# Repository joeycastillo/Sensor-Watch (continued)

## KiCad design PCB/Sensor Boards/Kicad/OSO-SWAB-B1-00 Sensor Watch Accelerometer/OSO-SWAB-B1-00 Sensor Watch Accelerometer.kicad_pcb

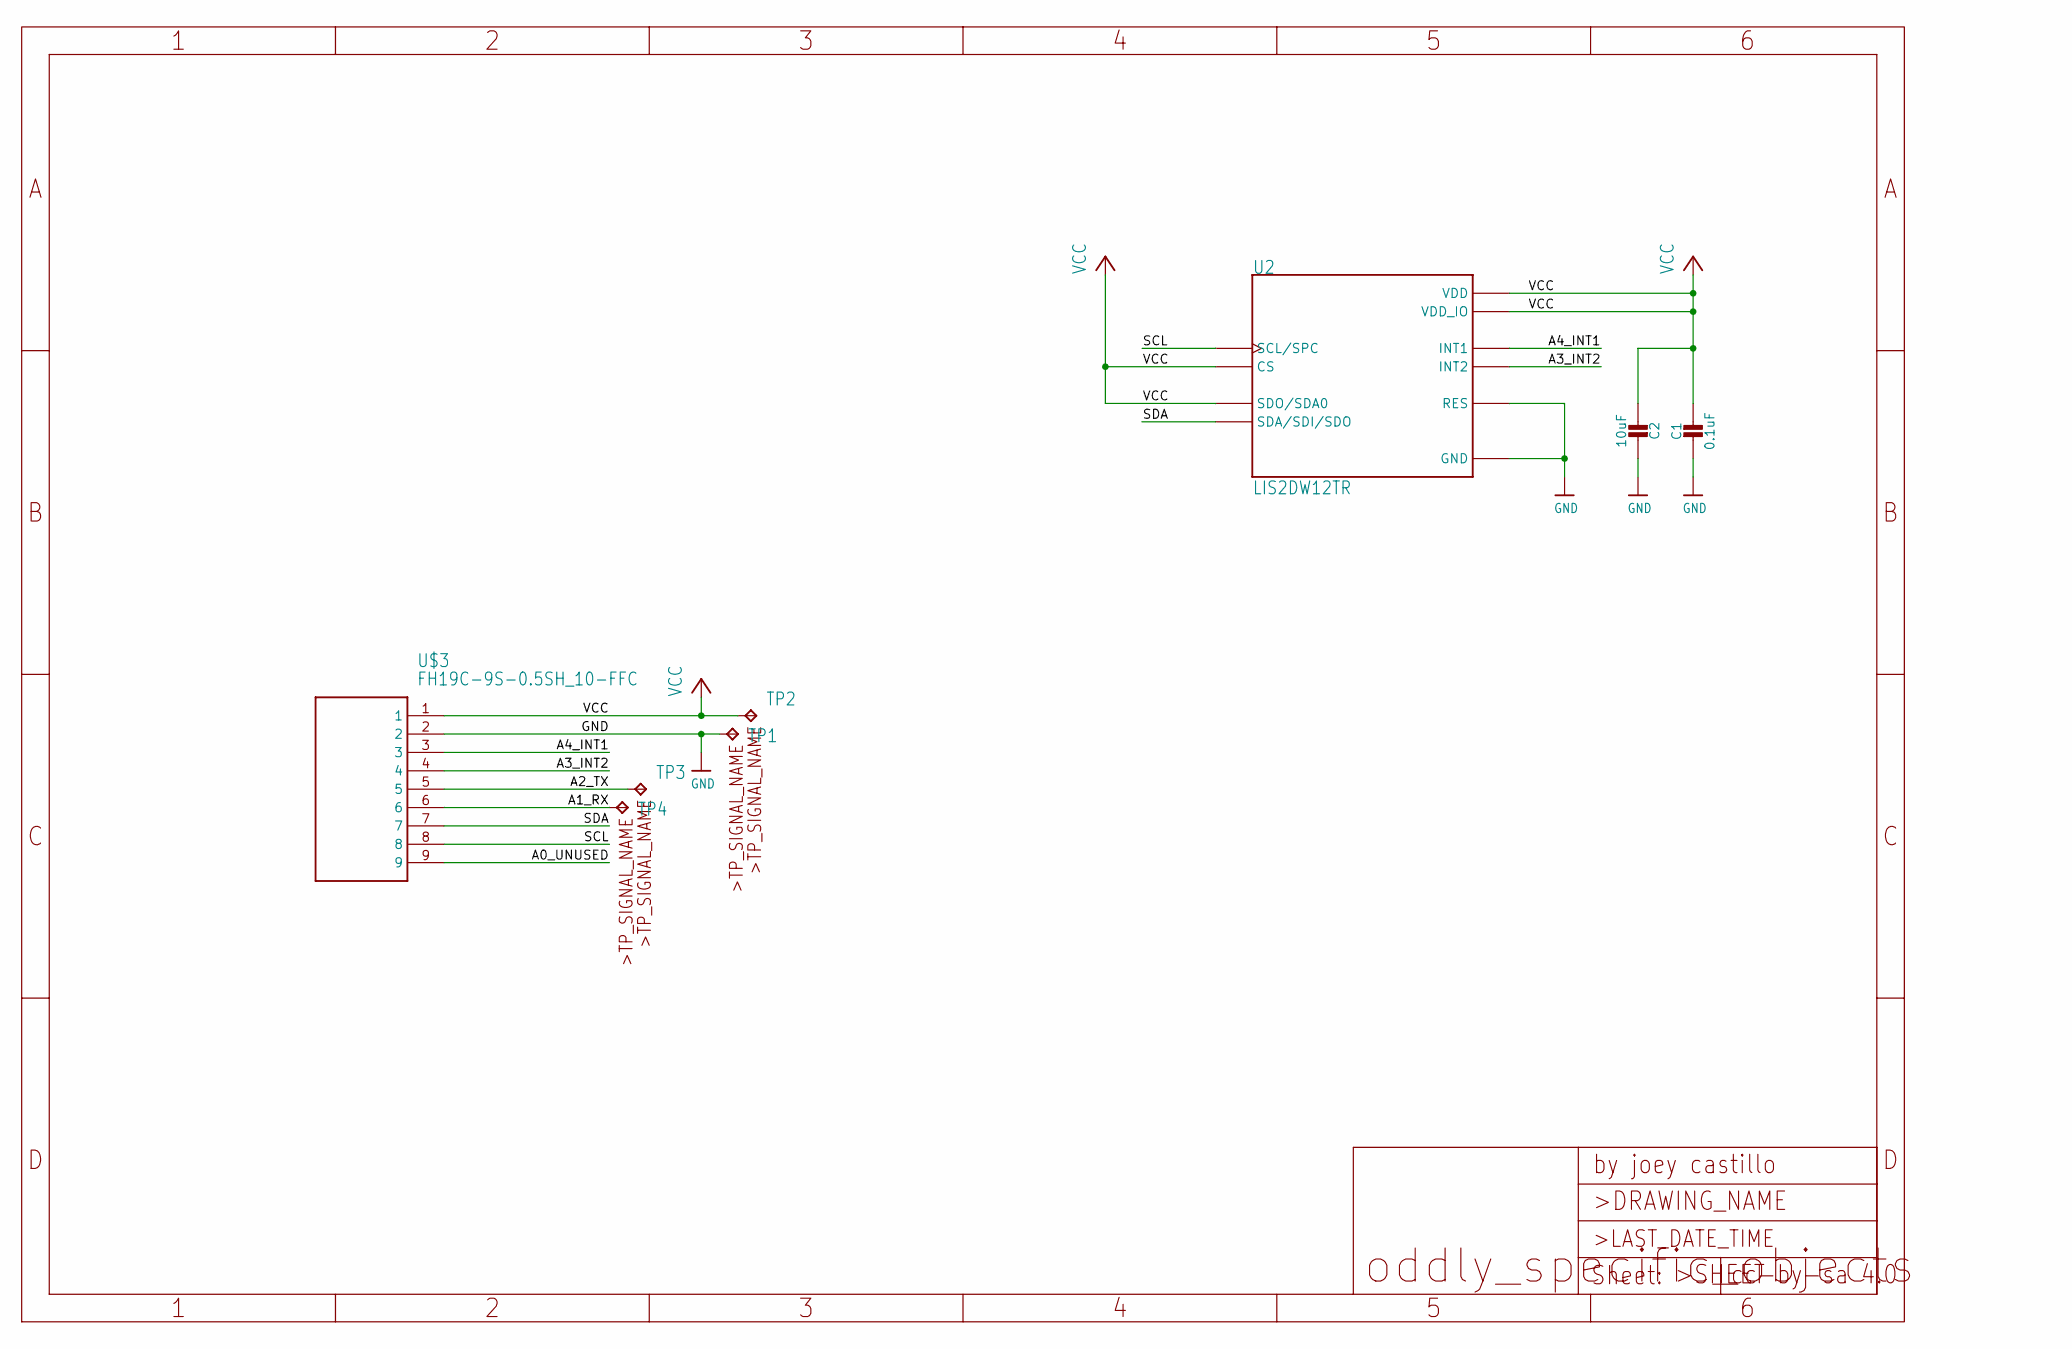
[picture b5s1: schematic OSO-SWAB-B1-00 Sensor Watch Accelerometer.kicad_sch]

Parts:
C1: 0.1uF; _0603MP
C2: 10uF; _0603MP
TP1, TP2, TP3, TP4: TPB1,27; B1,27
U2: LIS2DW12TR; LGA12R50P4X4_200X200X70
U$3: FH19C-9S-0.5SH_10-FFC; FH19C9S05SH10-FFC

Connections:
/A0_UNUSED: U$3.9
/A1_RX: TP4.TP, U$3.6
/A2_TX: TP3.TP, U$3.5
/A3_INT2: U2.11 (INT2), U$3.4
/A4_INT1: U2.12 (INT1), U$3.3
/SCL: U2.1 (SCL/SPC), U$3.8
/SDA: U2.4 (SDA/SDI/SDO), U$3.7
GND: C1.2, C2.1, TP1.TP, U2.6 (GND), U2.7 (RES), U2.8 (GND), U$3.2
VCC: C1.1, C2.2, TP2.TP, U2.2 (CS), U2.3 (SDO/SDA0), U2.9 (VDD), U2.10 (VDD_IO), U$3.1

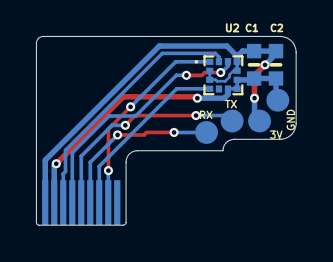
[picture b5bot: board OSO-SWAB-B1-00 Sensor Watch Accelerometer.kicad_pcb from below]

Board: 2 copper layers, 14.4 x 10.5 mm, 8 parts (7 on the bottom side), 8 nets.

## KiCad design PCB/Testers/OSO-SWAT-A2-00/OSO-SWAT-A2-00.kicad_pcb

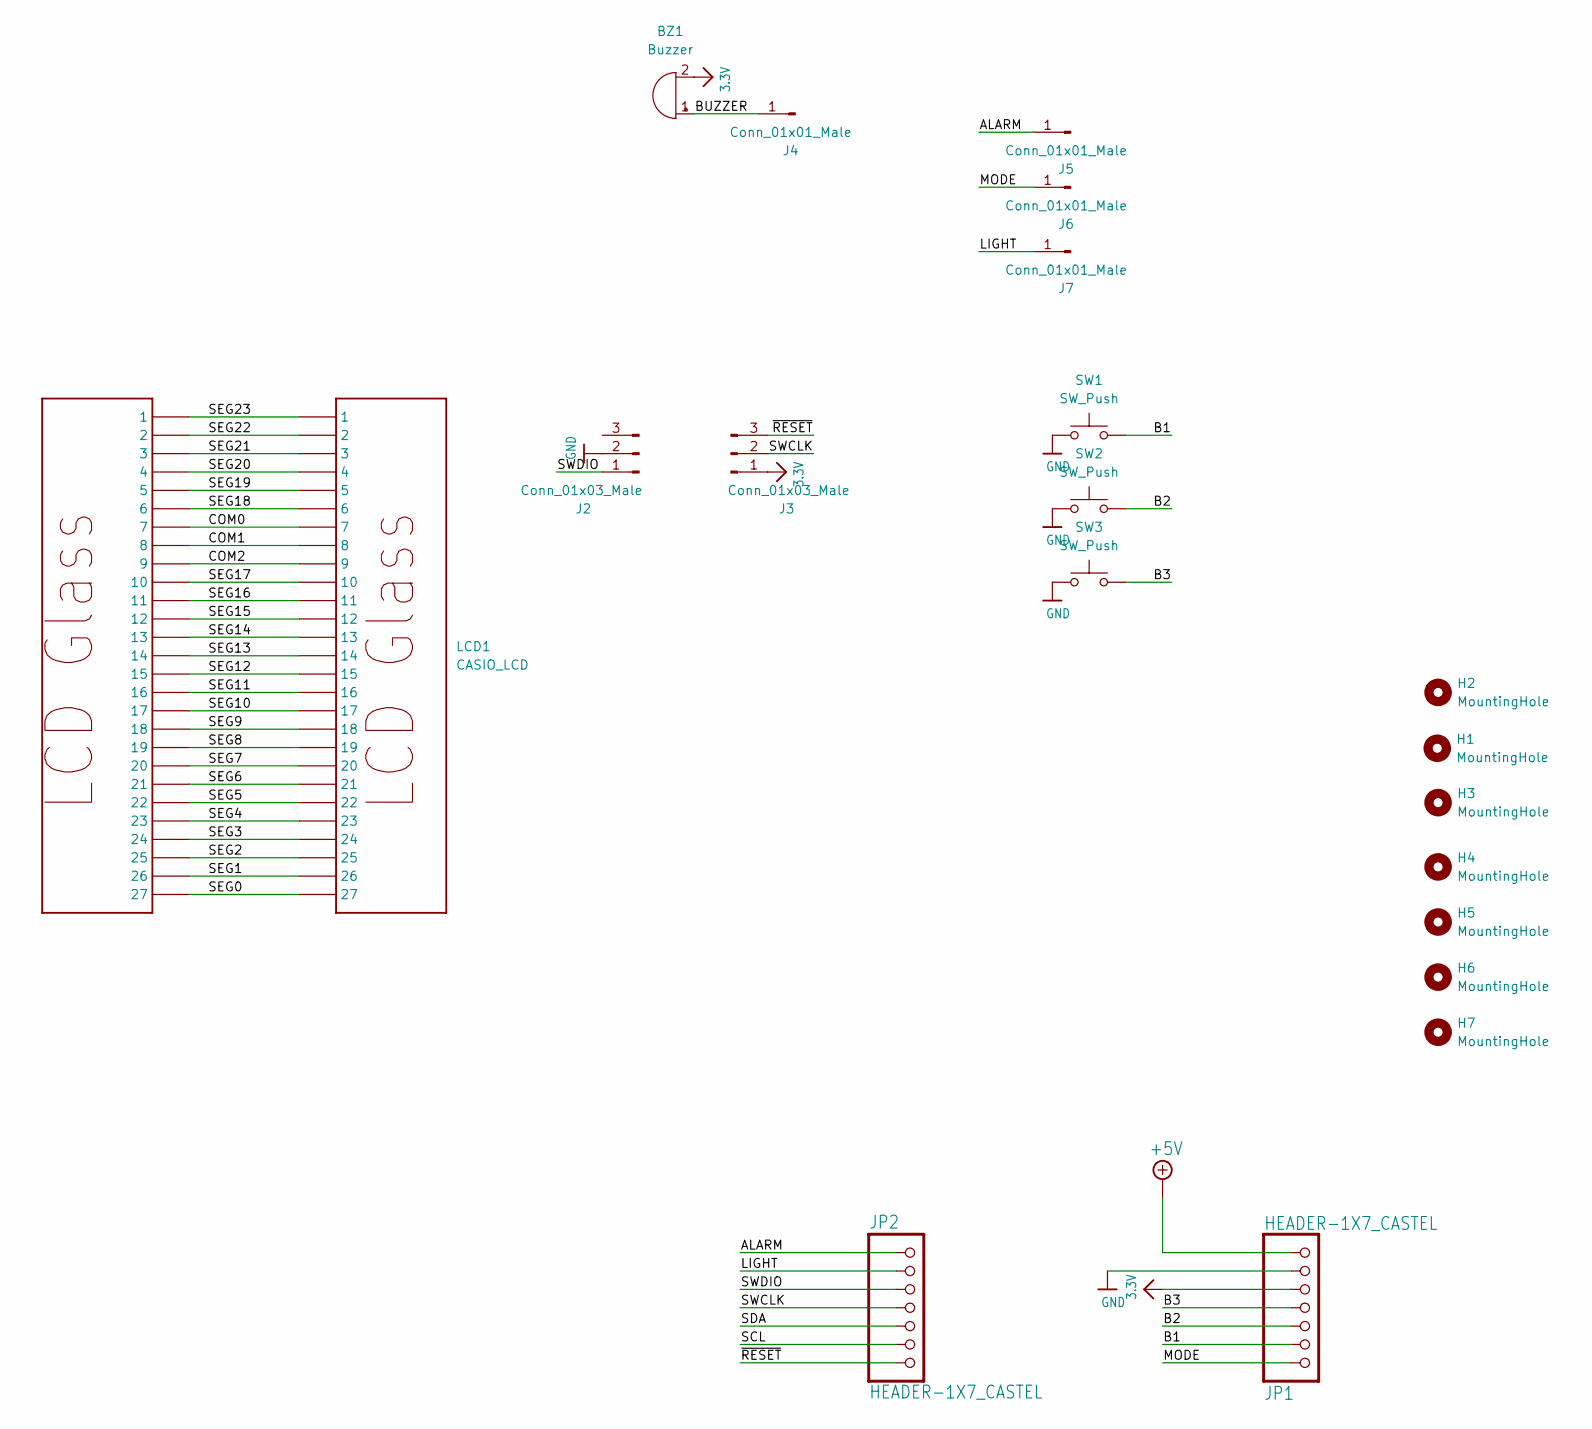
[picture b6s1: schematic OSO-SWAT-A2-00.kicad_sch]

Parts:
BZ1: Buzzer
H1, H2, H3, H4, H5, H6: MountingHole
H7: MountingHole; MountingHole_2.7mm_M2.5
J2, J3: Conn_01x03_Male; PinHeader_1x03_P2.54mm_Vertical
J4: Conn_01x01_Male; PinHeader_1x01_P2.54mm_Vertical
J5, J6, J7: Conn_01x01_Male; FlexyPin_1x01_P2.54mm
JP1, JP2: HEADER-1X7_CASTEL; 1X07_CASTEL
LCD1: CASIO_LCD; CASIO-F91W-LCD
SW1, SW2, SW3: SW_Push
U1: LCD_FEATHER_DISPLAY

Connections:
3.3V: BZ1.2 (+), J3.1, JP1.5, JP1.5C (5)
+5V: JP1.7, JP1.7C (7)
/ALARM: J5.1, JP2.1, JP2.1C (1)
/B1: JP1.2, JP1.2C (2), SW1.2
/B2: JP1.3, JP1.3C (3), SW2.2
/B3: JP1.4, JP1.4C (4), SW3.2
/BUZZER: BZ1.1 (-), J4.1
/COM0: LCD1.7, U1.P$7 (7)
/COM1: LCD1.8, U1.P$8 (8)
/COM2: LCD1.9, U1.P$9 (9)
/LIGHT: J7.1, JP2.2, JP2.2C (2)
/MODE: J6.1, JP1.1, JP1.1C (1)
/SCL: JP2.6, JP2.6C (6)
/SDA: JP2.5, JP2.5C (5)
/SEG0: LCD1.27, U1.P$27 (27)
/SEG1: LCD1.26, U1.P$26 (26)
/SEG2: LCD1.25, U1.P$25 (25)
/SEG3: LCD1.24, U1.P$24 (24)
/SEG4: LCD1.23, U1.P$23 (23)
/SEG5: LCD1.22, U1.P$22 (22)
/SEG6: LCD1.21, U1.P$21 (21)
/SEG7: LCD1.20, U1.P$20 (20)
/SEG8: LCD1.19, U1.P$19 (19)
/SEG9: LCD1.18, U1.P$18 (18)
/SEG10: LCD1.17, U1.P$17 (17)
/SEG11: LCD1.16, U1.P$16 (16)
/SEG12: LCD1.15, U1.P$15 (15)
/SEG13: LCD1.14, U1.P$14 (14)
/SEG14: LCD1.13, U1.P$13 (13)
/SEG15: LCD1.12, U1.P$12 (12)
/SEG16: LCD1.11, U1.P$11 (11)
/SEG17: LCD1.10, U1.P$10 (10)
/SEG18: LCD1.6, U1.P$6 (6)
/SEG19: LCD1.5, U1.P$5 (5)
/SEG20: LCD1.4, U1.P$4 (4)
/SEG21: LCD1.3, U1.P$3 (3)
/SEG22: LCD1.2, U1.P$2 (2)
/SEG23: LCD1.1, U1.P$1 (1)
/SWCLK: J3.2, JP2.4, JP2.4C (4)
/SWDIO: J2.1, JP2.3, JP2.3C (3)
/~RESET: J3.3, JP2.7, JP2.7C (7)
GND: J2.2, JP1.6, JP1.6C (6), SW1.1, SW2.1, SW3.1

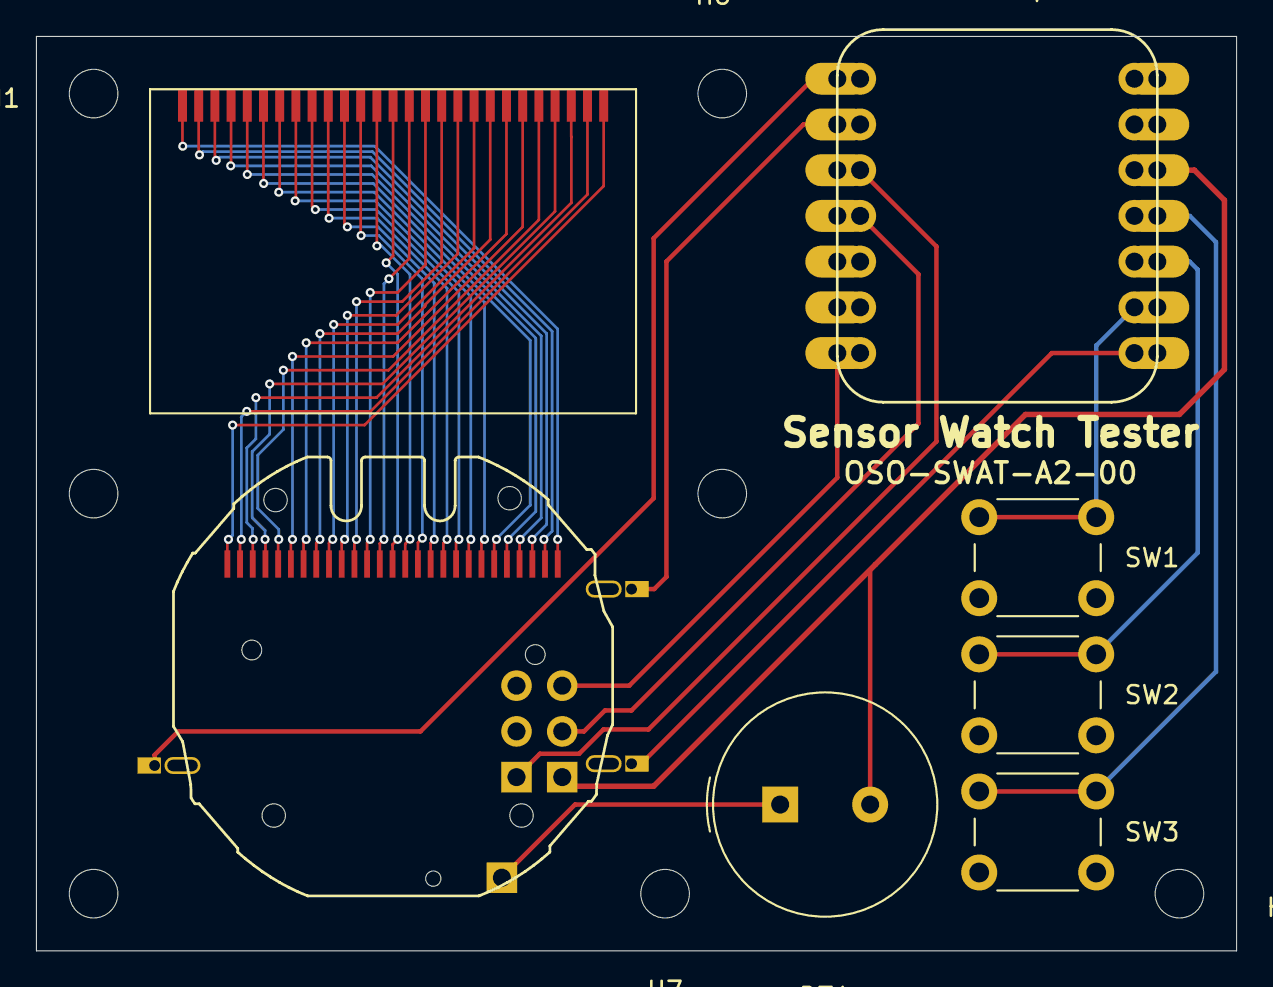
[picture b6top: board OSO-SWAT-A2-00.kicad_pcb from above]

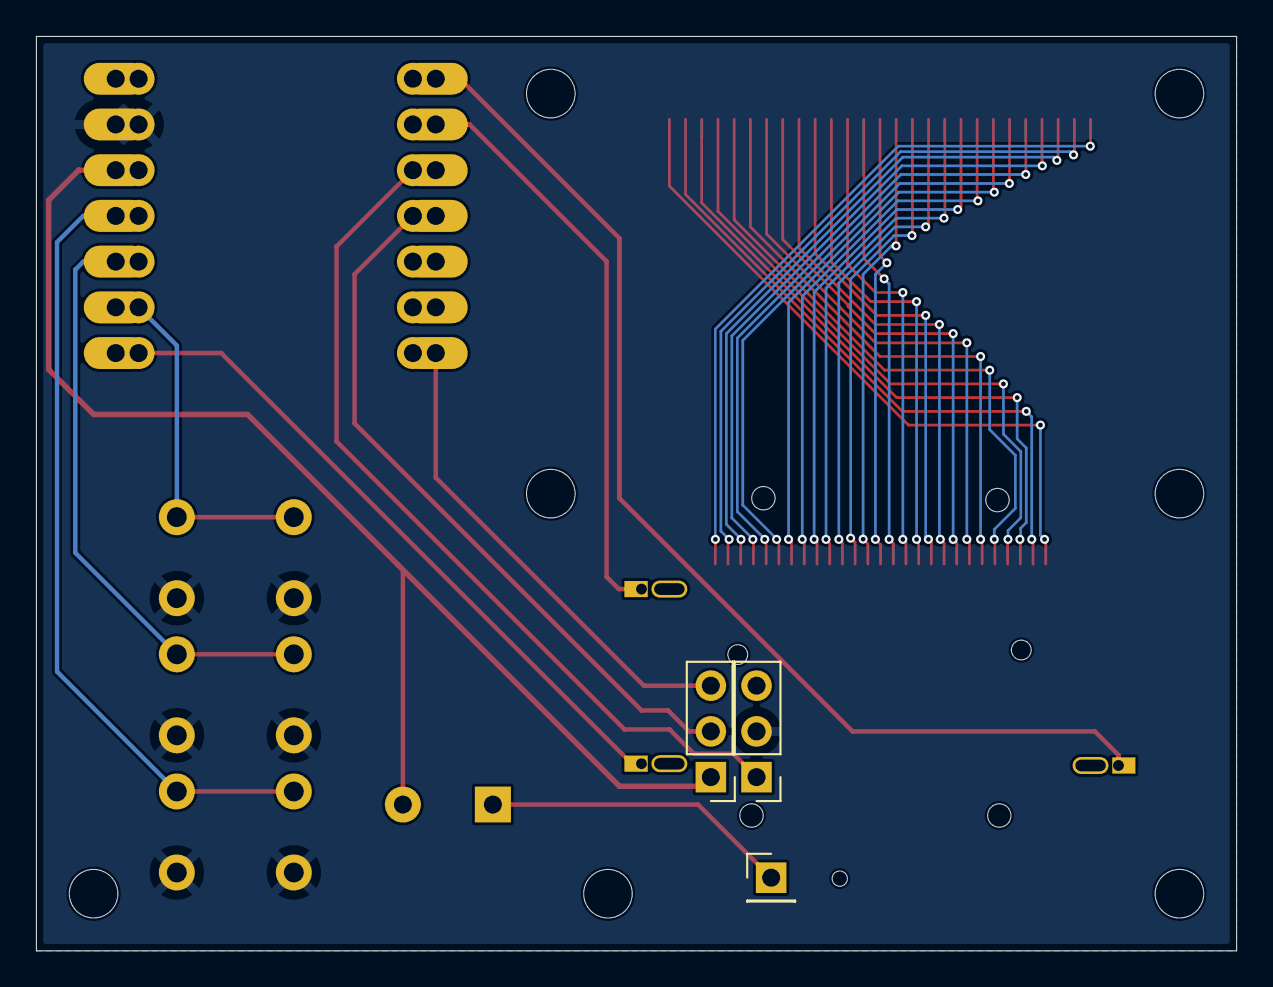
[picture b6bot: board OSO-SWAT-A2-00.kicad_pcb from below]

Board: 2 copper layers, 66.7 x 50.8 mm, 21 parts (7 on the bottom side), 42 nets.

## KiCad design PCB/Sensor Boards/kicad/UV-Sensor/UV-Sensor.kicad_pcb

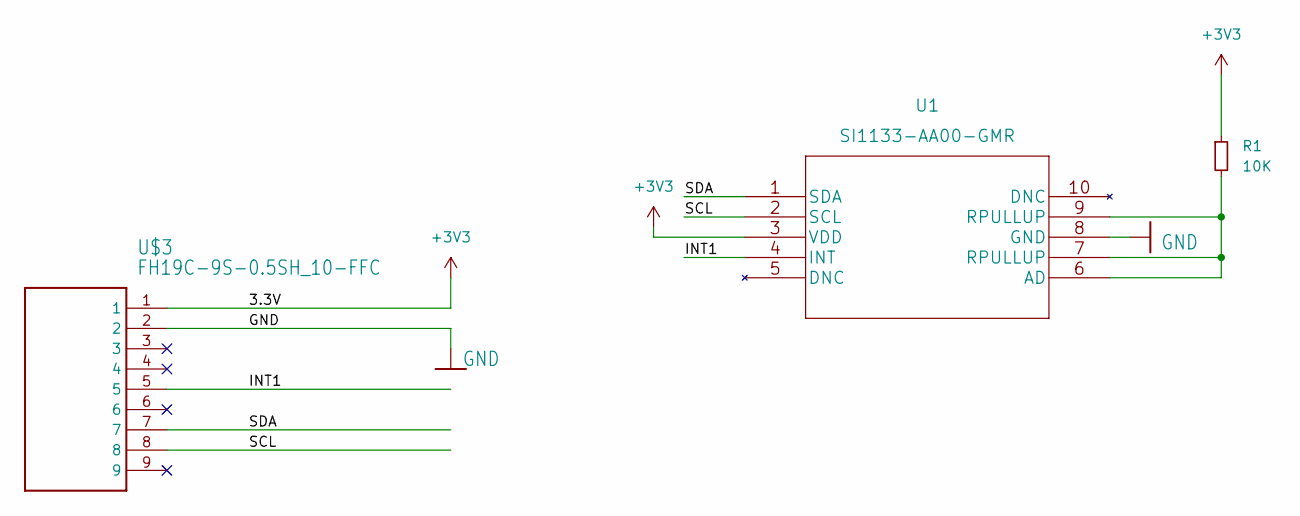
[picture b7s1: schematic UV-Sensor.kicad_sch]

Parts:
R1: 10K; R_0603_1608Metric_Pad0.98x0.95mm_HandSolder
U1: SI1133-AA00-GMR
U$3: FH19C-9S-0.5SH_10-FFC; FH19C9S05SH10-FFC

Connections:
+3V3: R1.1, U1.3 (VDD), U$3.1
/INT1: U1.4 (INT), U$3.5
/SCL: U1.2 (SCL), U$3.8
/SDA: U1.1 (SDA), U$3.7
GND: U1.8 (GND), U$3.2
unnamed: R1.2, U1.6 (AD), U1.7 (RPULLUP), U1.9 (RPULLUP)

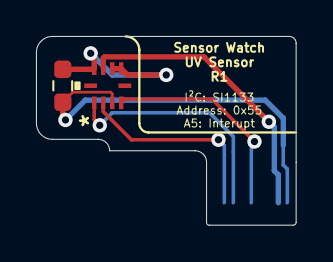
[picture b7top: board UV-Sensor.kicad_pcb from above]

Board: 4 copper layers, 14.4 x 10.5 mm, 3 parts (0 on the bottom side), 6 nets.

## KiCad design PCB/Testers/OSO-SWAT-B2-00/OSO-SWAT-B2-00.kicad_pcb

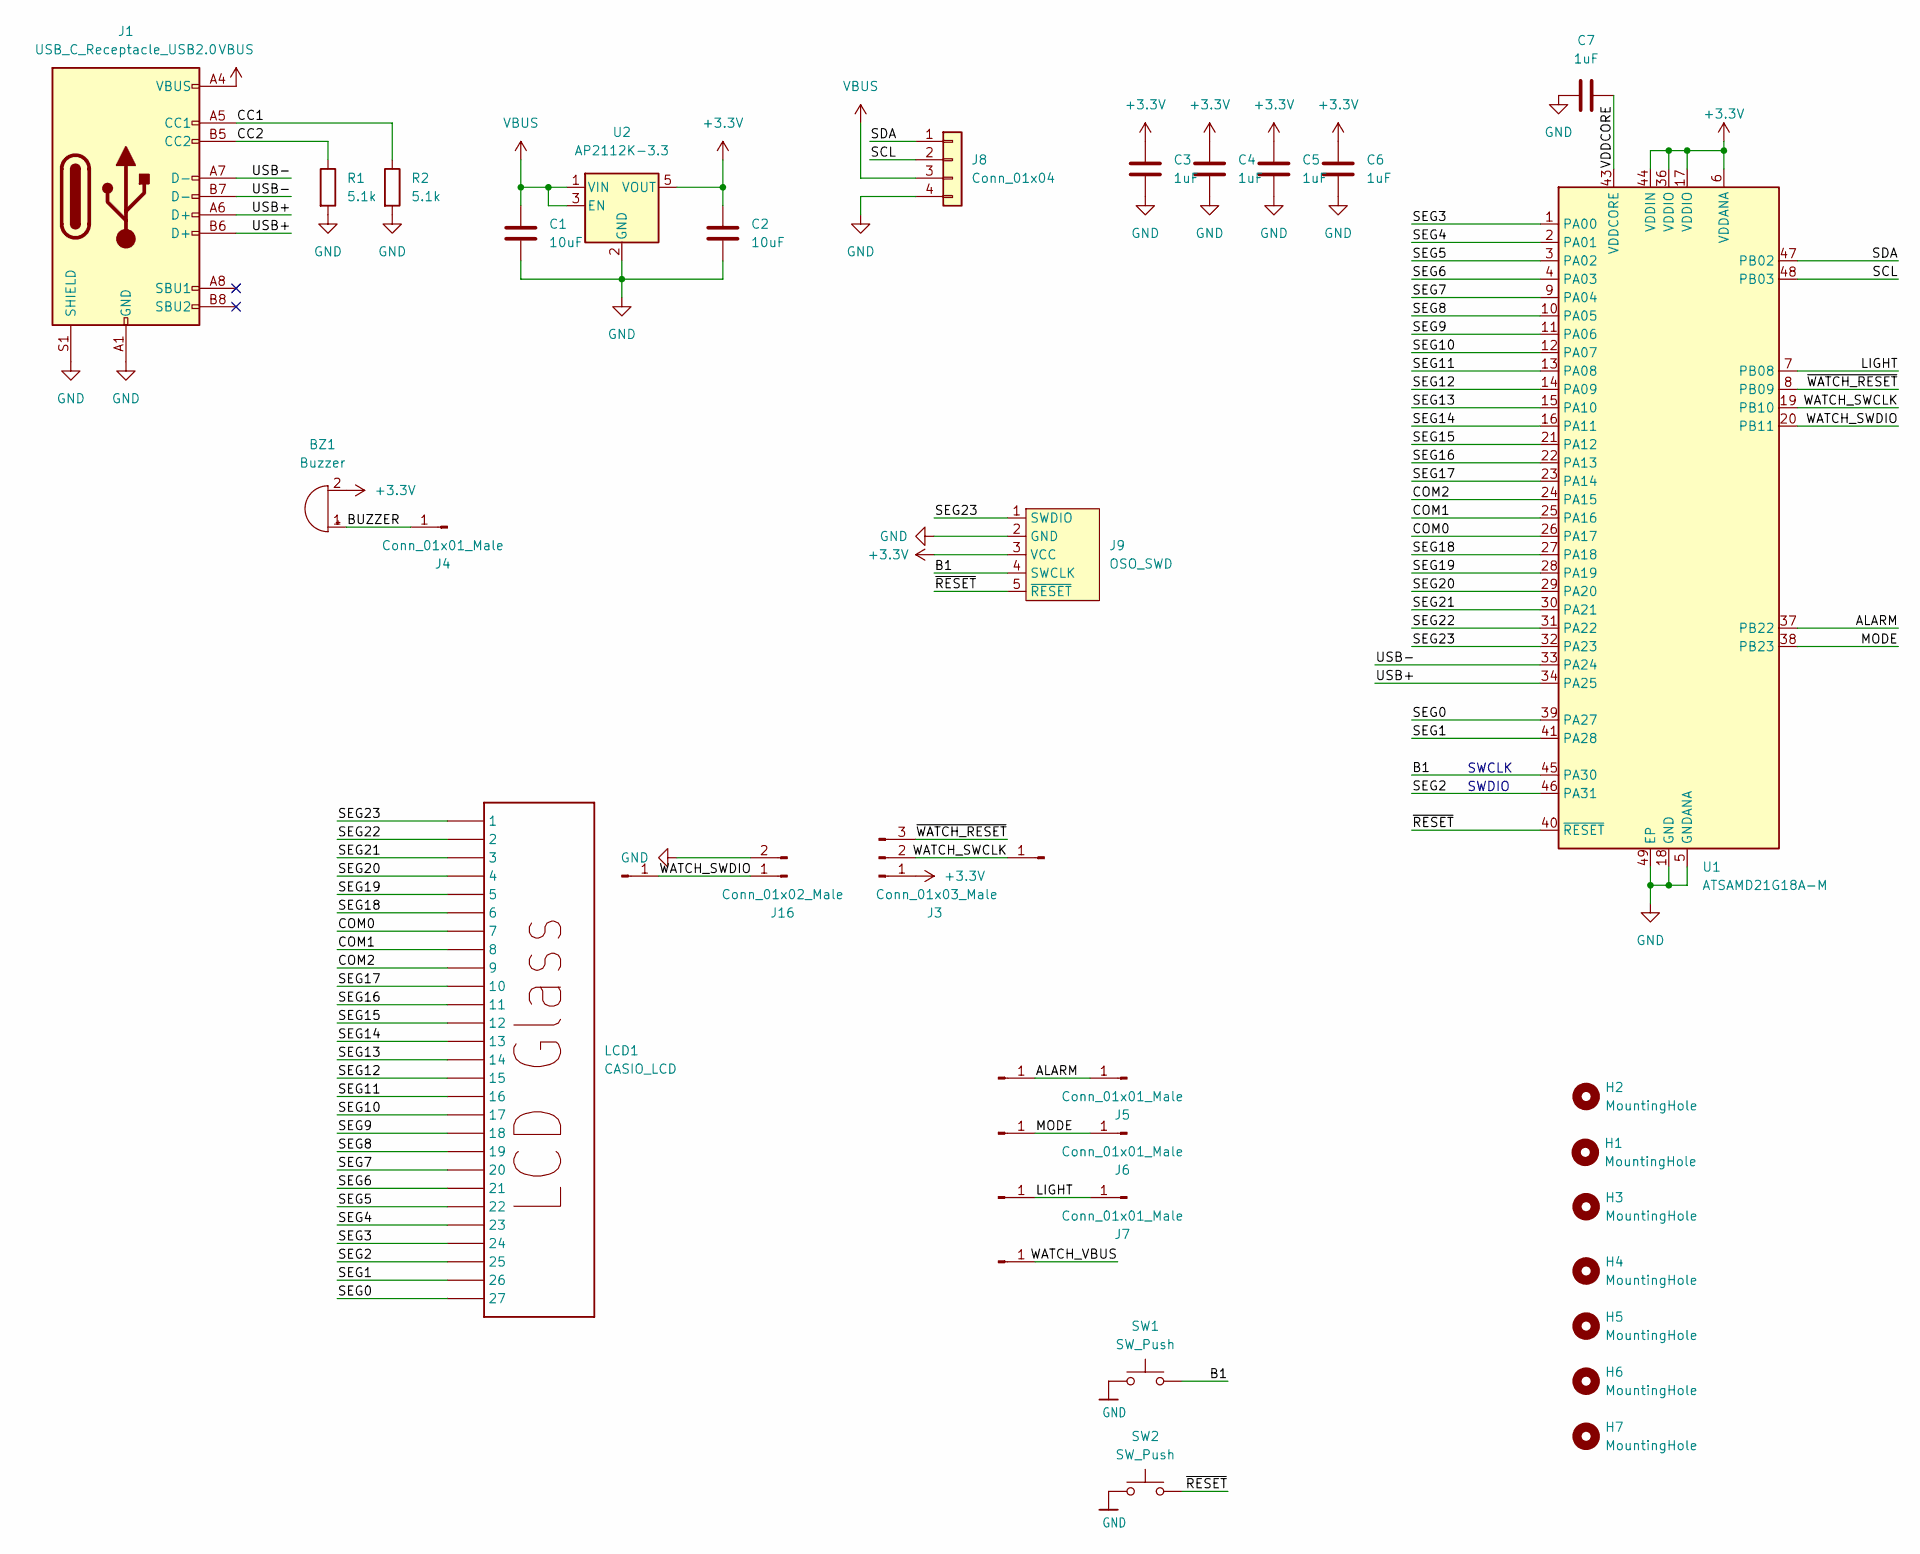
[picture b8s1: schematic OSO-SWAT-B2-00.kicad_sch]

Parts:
BZ1: Buzzer; Buzzer_TDK_PS1240P02BT_D12.2mm_H6.5mm
C1, C2: 10uF; C_0805_2012Metric_Pad1.18x1.45mm_HandSolder
C3, C4, C5, C6, C7: 1uF; C_0805_2012Metric_Pad1.18x1.45mm_HandSolder
H1, H2, H3, H4, H5, H6, H7: MountingHole; MountingHole_2.7mm_M2.5
J1: USB_C_Receptacle_USB2.0; USB_C_Receptacle_HRO_TYPE-C-31-M-12
J3: Conn_01x03_Male; PinHeader_1x03_P2.54mm_Vertical
J4, J10, J11, J12, J13, J14, J15: Conn_01x01_Male; PinHeader_1x01_P2.54mm_Vertical
J5, J6, J7: Conn_01x01_Male; FlexyPin_1x01_P2.54mm
J8: Conn_01x04; TerminalBlock_TE_282834-4_1x04_P2.54mm_Horizontal
J9: OSO_SWD; OSO_SWD_Linear
J16: Conn_01x02_Male; PinHeader_1x02_P2.54mm_Vertical
LCD1: CASIO_LCD; CASIO-F91W-LCD
R1, R2: 5.1k; R_0805_2012Metric_Pad1.20x1.40mm_HandSolder
SW1, SW2: SW_Push; SW_PUSH_6mm
U1: ATSAMD21G18A-M; QFN-48-1EP_7x7mm_P0.5mm_EP5.15x5.15mm
U2: AP2112K-3.3; SOT-23-5

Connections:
+3.3V: BZ1.2 (+), C2.2, C3.2, C4.2, C5.2, C6.2, J3.1, J9.3 (VCC), U1.6 (VDDANA), U1.17 (VDDIO), U1.36 (VDDIO), U1.44 (VDDIN), U2.5 (VOUT)
/ALARM: J5.1, J10.1, U1.37 (PB22)
/B1: J9.4 (SWCLK), SW1.2, U1.45 (PA30)
/BUZZER: BZ1.1 (-), J4.1
/CC1: J1.A5 (CC1), R2.1
/CC2: J1.B5 (CC2), R1.1
/COM0: LCD1.7, U1.26 (PA17)
/COM1: LCD1.8, U1.25 (PA16)
/COM2: LCD1.9, U1.24 (PA15)
/LIGHT: J7.1, J12.1, U1.7 (PB08)
/MODE: J6.1, J11.1, U1.38 (PB23)
/SCL: J8.2, U1.48 (PB03)
/SDA: J8.1, U1.47 (PB02)
/SEG0: LCD1.27, U1.39 (PA27)
/SEG1: LCD1.26, U1.41 (PA28)
/SEG2: LCD1.25, U1.46 (PA31)
/SEG3: LCD1.24, U1.1 (PA00)
/SEG4: LCD1.23, U1.2 (PA01)
/SEG5: LCD1.22, U1.3 (PA02)
/SEG6: LCD1.21, U1.4 (PA03)
/SEG7: LCD1.20, U1.9 (PA04)
/SEG8: LCD1.19, U1.10 (PA05)
/SEG9: LCD1.18, U1.11 (PA06)
/SEG10: LCD1.17, U1.12 (PA07)
/SEG11: LCD1.16, U1.13 (PA08)
/SEG12: LCD1.15, U1.14 (PA09)
/SEG13: LCD1.14, U1.15 (PA10)
/SEG14: LCD1.13, U1.16 (PA11)
/SEG15: LCD1.12, U1.21 (PA12)
/SEG16: LCD1.11, U1.22 (PA13)
/SEG17: LCD1.10, U1.23 (PA14)
/SEG18: LCD1.6, U1.27 (PA18)
/SEG19: LCD1.5, U1.28 (PA19)
/SEG20: LCD1.4, U1.29 (PA20)
/SEG21: LCD1.3, U1.30 (PA21)
/SEG22: LCD1.2, U1.31 (PA22)
/SEG23: J9.1 (SWDIO), LCD1.1, U1.32 (PA23)
/USB+: J1.A6 (D+), J1.B6 (D+), U1.34 (PA25)
/USB-: J1.A7 (D-), J1.B7 (D-), U1.33 (PA24)
/VDDCORE: C7.2, U1.43 (VDDCORE)
/WATCH_SWCLK: J3.2, J14.1, U1.19 (PB10)
/WATCH_SWDIO: J15.1, J16.1, U1.20 (PB11)
/WATCH_VBUS: J13.1
/~RESET: J9.5 (~RESET), SW2.2, U1.40 (~RESET)
/~WATCH_RESET: J3.3, U1.8 (PB09)
GND: C1.1, C2.1, C3.1, C4.1, C5.1, C6.1, C7.1, J1.A1 (GND), J1.A12 (GND), J1.B1 (GND), J1.B12 (GND), J1.S1 (SHIELD), J8.4, J9.2 (GND), J16.2, R1.2, R2.2, SW1.1, SW2.1, U1.5 (GNDANA), U1.18 (GND), U1.35 (GND), U1.42 (GND), U1.49 (EP), U2.2 (GND)
VBUS: C1.2, J1.A4 (VBUS), J1.A9 (VBUS), J1.B4 (VBUS), J1.B9 (VBUS), J8.3, U2.1 (VIN), U2.3 (EN)

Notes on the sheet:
SWDIO
SWCLK

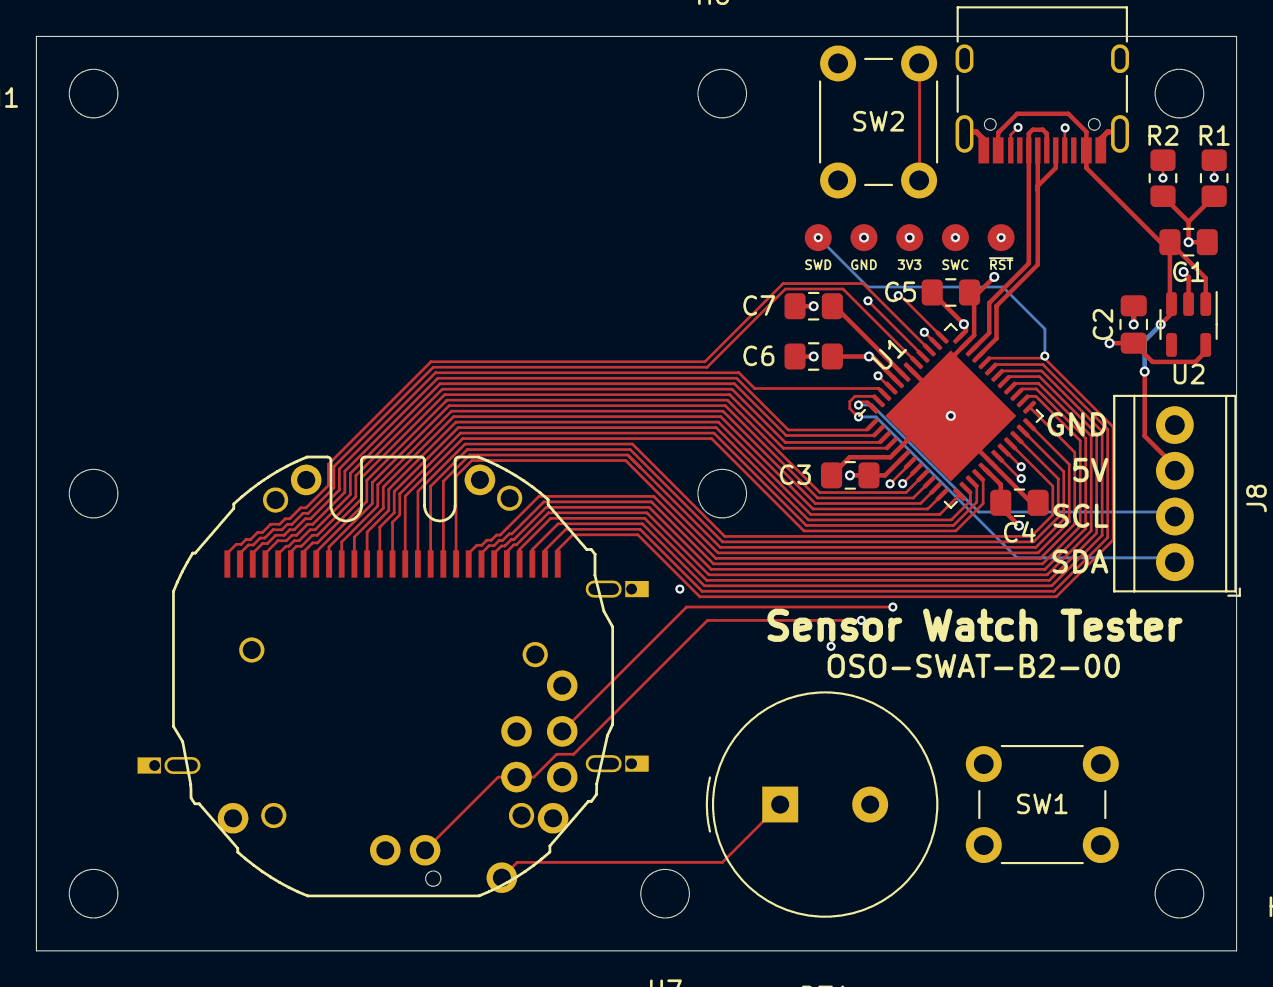
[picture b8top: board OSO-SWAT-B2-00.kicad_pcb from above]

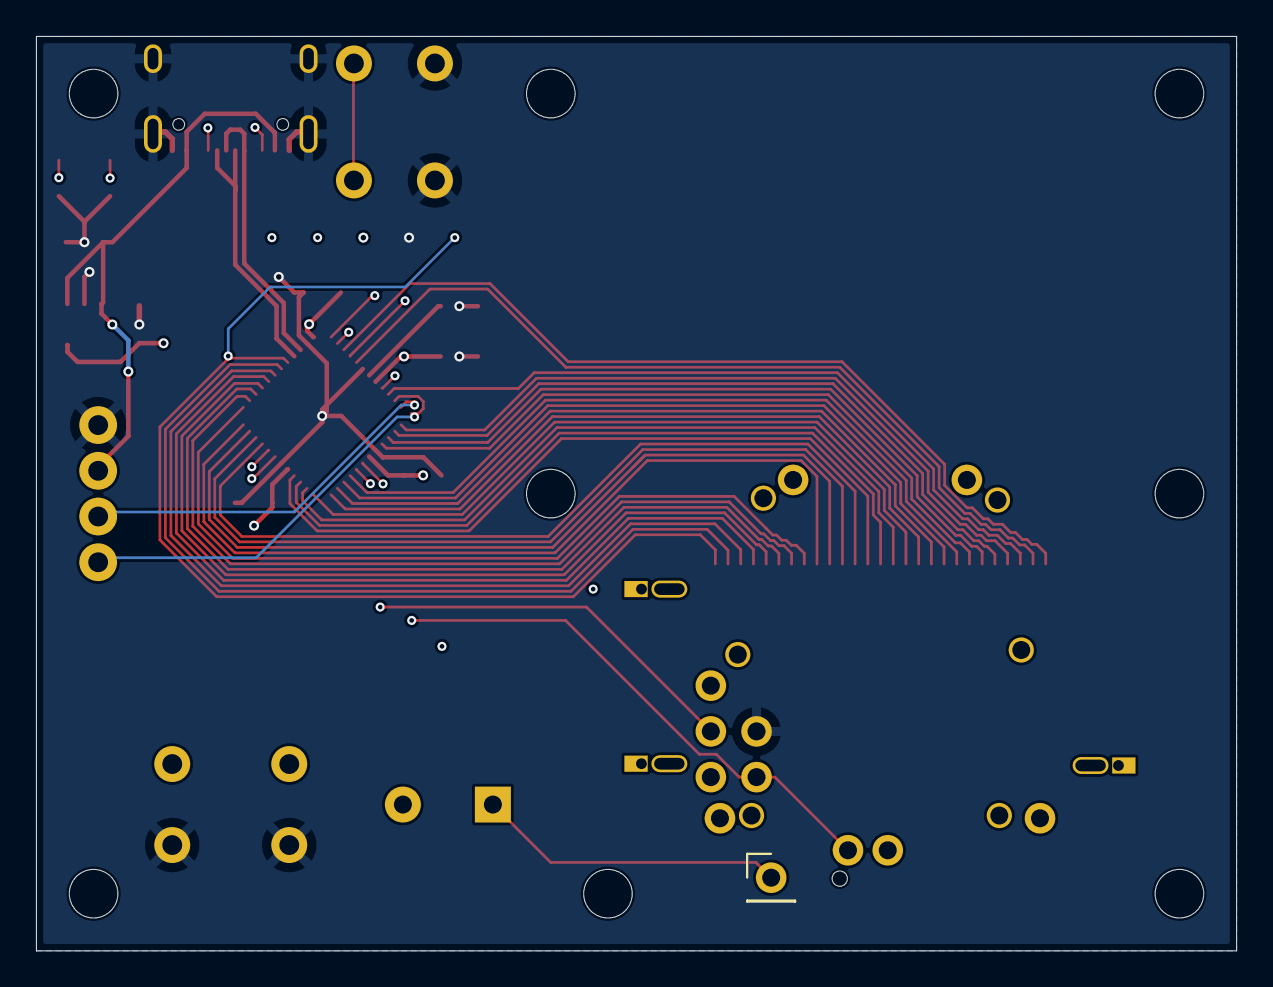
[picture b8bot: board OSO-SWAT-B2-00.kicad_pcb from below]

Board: 4 copper layers, 66.7 x 50.8 mm, 38 parts (5 on the bottom side), 46 nets.

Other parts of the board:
H2#2: MountingHole; MountingHole_2.7mm_M2.5

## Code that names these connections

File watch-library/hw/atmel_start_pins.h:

/*
 * Code generated from Atmel Start.
 *
 * This file will be overwritten when reconfiguring your Atmel Start project.
 * Please copy examples or other code you want to keep to a separate file
 * to avoid losing it when reconfiguring.
 */
#ifndef ATMEL_START_PINS_H_INCLUDED
#define ATMEL_START_PINS_H_INCLUDED

#include <hal_gpio.h>

// SAML22 has 9 pin functions

#define GPIO_PIN_FUNCTION_A 0
#define GPIO_PIN_FUNCTION_B 1
#define GPIO_PIN_FUNCTION_C 2
#define GPIO_PIN_FUNCTION_D 3
#define GPIO_PIN_FUNCTION_E 4
#define GPIO_PIN_FUNCTION_F 5
#define GPIO_PIN_FUNCTION_G 6
#define GPIO_PIN_FUNCTION_H 7
#define GPIO_PIN_FUNCTION_I 8

#define VBUS_DET GPIO(GPIO_PORTA, 3)
#define SEG1 GPIO(GPIO_PORTA, 4)
#define SEG2 GPIO(GPIO_PORTA, 5)
#define SEG3 GPIO(GPIO_PORTA, 6)
#define SEG4 GPIO(GPIO_PORTA, 7)
#define SEG5 GPIO(GPIO_PORTA, 8)
#define SEG6 GPIO(GPIO_PORTA, 9)
#define SEG7 GPIO(GPIO_PORTA, 10)
#define SEG8 GPIO(GPIO_PORTA, 11)
#define SEG14 GPIO(GPIO_PORTA, 12)
#define SEG15 GPIO(GPIO_PORTA, 13)
#define SEG16 GPIO(GPIO_PORTA, 14)
#define SEG17 GPIO(GPIO_PORTA, 15)
#define SEG18 GPIO(GPIO_PORTA, 16)
#define SEG19 GPIO(GPIO_PORTA, 17)
#define SEG20 GPIO(GPIO_PORTA, 18)
#define SEG21 GPIO(GPIO_PORTA, 19)
#ifdef WATCH_SWAP_LED_PINS
    #define RED GPIO(GPIO_PORTA, 21)
    #define GREEN GPIO(GPIO_PORTA, 20)
#else
    #define RED GPIO(GPIO_PORTA, 20)
    #define GREEN GPIO(GPIO_PORTA, 21)
#endif
#define BTN_ALARM GPIO(GPIO_PORTA, 2)
#define BTN_LIGHT GPIO(GPIO_PORTA, 22)
#define BTN_MODE GPIO(GPIO_PORTA, 23)
#define BUZZER GPIO(GPIO_PORTA, 27)
#define A0 GPIO(GPIO_PORTB, 4)
#define A1 GPIO(GPIO_PORTB, 1)
#define A2 GPIO(GPIO_PORTB, 2)
#define A3 GPIO(GPIO_PORTB, 3)
#define A4 GPIO(GPIO_PORTB, 0)
#define D0 GPIO(GPIO_PORTB, 3)
#define D1 GPIO(GPIO_PORTB, 0)
#define COM0 GPIO(GPIO_PORTB, 6)
#define COM1 GPIO(GPIO_PORTB, 7)
#define COM2 GPIO(GPIO_PORTB, 8)
#define SEG0 GPIO(GPIO_PORTB, 9)
#define SEG9 GPIO(GPIO_PORTB, 11)
#define SEG10 GPIO(GPIO_PORTB, 12)
#define SEG11 GPIO(GPIO_PORTB, 13)
#define SEG12 GPIO(GPIO_PORTB, 14)
#define SEG13 GPIO(GPIO_PORTB, 15)
#define SEG22 GPIO(GPIO_PORTB, 16)
#define SEG23 GPIO(GPIO_PORTB, 17)
#define SDA GPIO(GPIO_PORTB, 30)
#define SCL GPIO(GPIO_PORTB, 31)

#endif // ATMEL_START_PINS_H_INCLUDED

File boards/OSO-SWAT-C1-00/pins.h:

#ifndef PINS_H_INCLUDED
#define PINS_H_INCLUDED

// Detects if we are on USB power.
#define VBUS_DET GPIO(GPIO_PORTB, 5)

// Buttons
#define BTN_ALARM GPIO(GPIO_PORTA, 2)
#define WATCH_BTN_ALARM_EIC_CHANNEL 2
#define BTN_LIGHT GPIO(GPIO_PORTA, 30)
#define WATCH_BTN_LIGHT_EIC_CHANNEL 10
#define BTN_MODE GPIO(GPIO_PORTA, 31)
#define WATCH_BTN_MODE_EIC_CHANNEL 11

// Temperature Sensor
#define TS_ENABLE GPIO(GPIO_PORTB, 23)
#define TEMPSENSE GPIO(GPIO_PORTA, 3)

// Light Sensor
#define IR_ENABLE GPIO(GPIO_PORTB, 22)
#define IRSENSE GPIO(GPIO_PORTA, 4)

// Buzzer
#define BUZZER GPIO(GPIO_PORTA, 27)
#define WATCH_BUZZER_TCC_PINMUX PINMUX_PA27F_TCC0_WO5
#define WATCH_BUZZER_TCC_CHANNEL 1

// LEDs
#define WATCH_INVERT_LED_POLARITY

#define RED GPIO(GPIO_PORTA, 12)
#define WATCH_RED_TCC_CHANNEL 2
#define WATCH_RED_TCC_PINMUX PINMUX_PA12F_TCC0_WO6

#define BLUE GPIO(GPIO_PORTA, 13)
#define WATCH_BLUE_TCC_CHANNEL 3
#define WATCH_BLUE_TCC_PINMUX PINMUX_PA13F_TCC0_WO7

#define GREEN GPIO(GPIO_PORTA, 22)
#define WATCH_GREEN_TCC_CHANNEL 0
#define WATCH_GREEN_TCC_PINMUX PINMUX_PA22F_TCC0_WO4

// Segment LCD
#define SLCD0 GPIO(GPIO_PORTB, 6)
#define SLCD1 GPIO(GPIO_PORTB, 7)
#define SLCD2 GPIO(GPIO_PORTB, 8)
#define SLCD3 GPIO(GPIO_PORTB, 9)
#define SLCD4 GPIO(GPIO_PORTA, 5)
#define SLCD5 GPIO(GPIO_PORTA, 6)
#define SLCD6 GPIO(GPIO_PORTA, 7)
#define SLCD7 GPIO(GPIO_PORTA, 8)
#define SLCD8 GPIO(GPIO_PORTA, 9)
#define SLCD9 GPIO(GPIO_PORTA, 10)
#define SLCD10 GPIO(GPIO_PORTA, 11)
#define SLCD11 GPIO(GPIO_PORTB, 11)
#define SLCD12 GPIO(GPIO_PORTB, 12)
#define SLCD13 GPIO(GPIO_PORTB, 13)
#define SLCD14 GPIO(GPIO_PORTB, 14)
#define SLCD15 GPIO(GPIO_PORTB, 15)
#define SLCD16 GPIO(GPIO_PORTA, 14)
#define SLCD17 GPIO(GPIO_PORTA, 15)
#define SLCD18 GPIO(GPIO_PORTA, 16)
#define SLCD19 GPIO(GPIO_PORTA, 17)
#define SLCD20 GPIO(GPIO_PORTA, 18)
#define SLCD21 GPIO(GPIO_PORTA, 19)
#define SLCD22 GPIO(GPIO_PORTB, 16)
#define SLCD23 GPIO(GPIO_PORTB, 17)
#define SLCD24 GPIO(GPIO_PORTA, 20)
#define SLCD25 GPIO(GPIO_PORTA, 21)
#define SLCD26 GPIO(GPIO_PORTA, 23)
// This board uses a slightly different pin mapping from the standard watch, and it's not enough to
// just declare the pins. We also have to set the LCD Pin Enable register with the SLCD pins we're
// using. These numbers are not port/pin numbers, but the "SLCD/LP[x]" numbers in the pinmux table.
// If not defined in pins.h, the LCD driver will fall back to the pin mapping in hpl_slcd_config.h.
// LPENL is for pins SLCD/LP[0..31].
#define CONF_SLCD_LPENL (\
        (uint32_t)1 <<  0 | \
        (uint32_t)1 <<  1 | \
        (uint32_t)1 <<  2 | \
        (uint32_t)1 <<  3 | \
        (uint32_t)1 <<  5 | \
        (uint32_t)1 <<  6 | \
        (uint32_t)1 <<  7 | \
        (uint32_t)1 << 11 | \
        (uint32_t)1 << 12 | \
        (uint32_t)1 << 13 | \
        (uint32_t)1 << 14 | \
        (uint32_t)1 << 21 | \
        (uint32_t)1 << 22 | \
        (uint32_t)1 << 23 | \
        (uint32_t)1 << 24 | \
        (uint32_t)1 << 25 | \
        (uint32_t)1 << 30 | \
        (uint32_t)1 << 31 | 0)
// LPENH is for pins SLCD/LP[32..51], where bit 0 represents pin 32.
#define CONF_SLCD_LPENH (\
        (uint32_t)1 << (32 - 32) | \
        (uint32_t)1 << (33 - 32) | \
        (uint32_t)1 << (34 - 32) | \
        (uint32_t)1 << (35 - 32) | \
        (uint32_t)1 << (42 - 32) | \
        (uint32_t)1 << (43 - 32) | \
        (uint32_t)1 << (48 - 32) | \
        (uint32_t)1 << (49 - 32) | \
        (uint32_t)1 << (51 - 32) | 0)


// 9-pin connector
#define A0 GPIO(GPIO_PORTB, 4)
#define WATCH_A0_EIC_CHANNEL 4
#define A1 GPIO(GPIO_PORTB, 1)
#define WATCH_A1_EIC_CHANNEL 1
#define A2 GPIO(GPIO_PORTB, 2)
#define WATCH_A2_EIC_CHANNEL 2
#define A3 GPIO(GPIO_PORTB, 3)
#define WATCH_A3_EIC_CHANNEL 3
#define A4 GPIO(GPIO_PORTB, 0)
#define WATCH_A4_EIC_CHANNEL 0
#define SDA GPIO(GPIO_PORTB, 30)
#define SCL GPIO(GPIO_PORTB, 31)

// aliases for as A3/A4; these were mentioned as D0/D1 in early documentation.
#define D0 GPIO(GPIO_PORTB, 3)
#define D1 GPIO(GPIO_PORTB, 0)

// interrupt mapping
#define EXT_IRQ_AMOUNT 6
#define CONFIG_EIC_EXTINT_MAP {0, PIN_PB00}, {1, PIN_PB01}, {2, PIN_PA02}, {3, PIN_PB03}, {10, PIN_PA30}, {11, PIN_PA31},

#endif // PINS_H_INCLUDED

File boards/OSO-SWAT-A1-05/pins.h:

#ifndef PINS_H_INCLUDED
#define PINS_H_INCLUDED

// Detects if we are on USB power.
#define VBUS_DET GPIO(GPIO_PORTB, 5)

// Buttons
#define BTN_ALARM GPIO(GPIO_PORTA, 2)
#define WATCH_BTN_ALARM_EIC_CHANNEL 2
#define BTN_LIGHT GPIO(GPIO_PORTA, 22)
#define WATCH_BTN_LIGHT_EIC_CHANNEL 6
#define BTN_MODE GPIO(GPIO_PORTA, 23)
#define WATCH_BTN_MODE_EIC_CHANNEL 7

// Buzzer
#define BUZZER GPIO(GPIO_PORTA, 27)
#define WATCH_BUZZER_TCC_PINMUX PINMUX_PA27F_TCC0_WO5
#define WATCH_BUZZER_TCC_CHANNEL 1

// LEDs
#ifdef WATCH_IS_BLUE_BOARD
    #define RED GPIO(GPIO_PORTA, 21)
    #define WATCH_RED_TCC_PINMUX PINMUX_PA21F_TCC0_WO7
    #define WATCH_RED_TCC_CHANNEL 3
    #define GREEN GPIO(GPIO_PORTA, 20)
    #define WATCH_GREEN_TCC_CHANNEL 2
    #define WATCH_GREEN_TCC_PINMUX PINMUX_PA20F_TCC0_WO6
#else
    #define RED GPIO(GPIO_PORTA, 20)
    #define WATCH_RED_TCC_PINMUX PINMUX_PA20F_TCC0_WO6
    #define WATCH_RED_TCC_CHANNEL 2
    #define GREEN GPIO(GPIO_PORTA, 21)
    #define WATCH_GREEN_TCC_CHANNEL 3
    #define WATCH_GREEN_TCC_PINMUX PINMUX_PA21F_TCC0_WO7
#endif

// Segment LCD
#define SLCD0 GPIO(GPIO_PORTB, 6)
#define SLCD1 GPIO(GPIO_PORTB, 7)
#define SLCD2 GPIO(GPIO_PORTB, 8)
#define SLCD3 GPIO(GPIO_PORTB, 9)
#define SLCD4 GPIO(GPIO_PORTA, 4)
#define SLCD5 GPIO(GPIO_PORTA, 5)
#define SLCD6 GPIO(GPIO_PORTA, 6)
#define SLCD7 GPIO(GPIO_PORTA, 7)
#define SLCD8 GPIO(GPIO_PORTA, 8)
#define SLCD9 GPIO(GPIO_PORTA, 9)
#define SLCD10 GPIO(GPIO_PORTA, 10)
#define SLCD11 GPIO(GPIO_PORTA, 11)
#define SLCD12 GPIO(GPIO_PORTB, 11)
#define SLCD13 GPIO(GPIO_PORTB, 12)
#define SLCD14 GPIO(GPIO_PORTB, 13)
#define SLCD15 GPIO(GPIO_PORTB, 14)
#define SLCD16 GPIO(GPIO_PORTB, 15)
#define SLCD17 GPIO(GPIO_PORTA, 12)
#define SLCD18 GPIO(GPIO_PORTA, 13)
#define SLCD19 GPIO(GPIO_PORTA, 14)
#define SLCD20 GPIO(GPIO_PORTA, 15)
#define SLCD21 GPIO(GPIO_PORTA, 16)
#define SLCD22 GPIO(GPIO_PORTA, 17)
#define SLCD23 GPIO(GPIO_PORTA, 18)
#define SLCD24 GPIO(GPIO_PORTA, 19)
#define SLCD25 GPIO(GPIO_PORTB, 16)
#define SLCD26 GPIO(GPIO_PORTB, 17)

// 9-pin connector
#define A0 GPIO(GPIO_PORTB, 4)
#define WATCH_A0_EIC_CHANNEL 4
#define A1 GPIO(GPIO_PORTB, 1)
#define WATCH_A1_EIC_CHANNEL 1
#define A2 GPIO(GPIO_PORTB, 2)
#define WATCH_A2_EIC_CHANNEL 2
#define A3 GPIO(GPIO_PORTB, 3)
#define WATCH_A3_EIC_CHANNEL 3
#define A4 GPIO(GPIO_PORTB, 0)
#define WATCH_A4_EIC_CHANNEL 0
#define SDA GPIO(GPIO_PORTB, 30)
#define SCL GPIO(GPIO_PORTB, 31)

// aliases for as A3/A4; these were mentioned as D0/D1 in early documentation.
#define D0 GPIO(GPIO_PORTB, 3)
#define D1 GPIO(GPIO_PORTB, 0)

// interrupt mapping
#define EXT_IRQ_AMOUNT 6
#define CONFIG_EIC_EXTINT_MAP {0, PIN_PB00}, {1, PIN_PB01}, {2, PIN_PA02}, {3, PIN_PB03}, {6, PIN_PA22}, {7, PIN_PA23},

#endif // PINS_H_INCLUDED

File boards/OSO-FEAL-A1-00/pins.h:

#ifndef PINS_H_INCLUDED
#define PINS_H_INCLUDED

// Detects if we are on USB power.
#define VBUS_DET GPIO(GPIO_PORTA, 3)

// Buttons
#define BTN_ALARM GPIO(GPIO_PORTA, 2)
#define WATCH_BTN_ALARM_EIC_CHANNEL 2
#define BTN_LIGHT GPIO(GPIO_PORTB, 5)
#define WATCH_BTN_LIGHT_EIC_CHANNEL 5
#define BTN_MODE GPIO(GPIO_PORTA, 7)
#define WATCH_BTN_MODE_EIC_CHANNEL 7

// Buzzer
#define BUZZER GPIO(GPIO_PORTA, 27)
#define WATCH_BUZZER_TCC_PINMUX PINMUX_PA27F_TCC0_WO5
#define WATCH_BUZZER_TCC_CHANNEL 1

// LEDs
#define WATCH_INVERT_LED_POLARITY
#define RED GPIO(GPIO_PORTA, 4)
#define WATCH_RED_TCC_CHANNEL 0
#define WATCH_RED_TCC_PINMUX PINMUX_PA04E_TCC0_WO0

#ifdef WATCH_IS_BLUE_BOARD
    #define GREEN GPIO(GPIO_PORTB, 22)
    #define WATCH_GREEN_TCC_CHANNEL 2
    #define WATCH_GREEN_TCC_PINMUX PINMUX_PB22F_TCC0_WO2
#else
    #define GREEN GPIO(GPIO_PORTB, 23)
    #define WATCH_GREEN_TCC_CHANNEL 3
    #define WATCH_GREEN_TCC_PINMUX PINMUX_PB23F_TCC0_WO3
#endif


// Segment LCD
// The LCD in this board can run comfortably at a lower voltage.
#define CONF_SLCD_CONTRAST_ADJUST 7

#define SLCD0 GPIO(GPIO_PORTB, 6)
#define SLCD1 GPIO(GPIO_PORTB, 7)
#define SLCD2 GPIO(GPIO_PORTB, 8)
#define SLCD3 GPIO(GPIO_PORTB, 9)
#define SLCD4 GPIO(GPIO_PORTA, 5)
#define SLCD5 GPIO(GPIO_PORTA, 6)
#define SLCD6 GPIO(GPIO_PORTA, 8)
#define SLCD7 GPIO(GPIO_PORTA, 9)
#define SLCD8 GPIO(GPIO_PORTA, 10)
#define SLCD9 GPIO(GPIO_PORTA, 11)
#define SLCD10 GPIO(GPIO_PORTB, 11)
#define SLCD11 GPIO(GPIO_PORTB, 12)
#define SLCD12 GPIO(GPIO_PORTB, 13)
#define SLCD13 GPIO(GPIO_PORTB, 14)
#define SLCD14 GPIO(GPIO_PORTB, 15)
#define SLCD15 GPIO(GPIO_PORTA, 14)
#define SLCD16 GPIO(GPIO_PORTA, 15)
#define SLCD17 GPIO(GPIO_PORTA, 16)
#define SLCD18 GPIO(GPIO_PORTA, 17)
#define SLCD19 GPIO(GPIO_PORTA, 18)
#define SLCD20 GPIO(GPIO_PORTA, 19)
#define SLCD21 GPIO(GPIO_PORTB, 16)
#define SLCD22 GPIO(GPIO_PORTB, 17)
#define SLCD23 GPIO(GPIO_PORTA, 20)
#define SLCD24 GPIO(GPIO_PORTA, 21)
#define SLCD25 GPIO(GPIO_PORTA, 22)
#define SLCD26 GPIO(GPIO_PORTA, 23)
// This board uses a slightly different pin mapping from the standard watch, and it's not enough to
// just declare the pins. We also have to set the LCD Pin Enable register with the SLCD pins we're
// using. These numbers are not port/pin numbers, but the "SLCD/LP[x]" numbers in the pinmux table.
// If not defined in pins.h, the LCD driver will fall back to the pin mapping in hpl_slcd_config.h.
// LPENL is for pins SLCD/LP[0..31].
#define CONF_SLCD_LPENL (\
        (uint32_t)1 <<  0 | \
        (uint32_t)1 <<  1 | \
        (uint32_t)1 <<  2 | \
        (uint32_t)1 <<  3 | \
        (uint32_t)1 <<  5 | \
        (uint32_t)1 <<  6 | \
        (uint32_t)1 << 11 | \
        (uint32_t)1 << 12 | \
        (uint32_t)1 << 13 | \
        (uint32_t)1 << 14 | \
        (uint32_t)1 << 21 | \
        (uint32_t)1 << 22 | \
        (uint32_t)1 << 23 | \
        (uint32_t)1 << 24 | \
        (uint32_t)1 << 25 | \
        (uint32_t)1 << 30 | \
        (uint32_t)1 << 31 | 0)
// LPENH is for pins SLCD/LP[32..51], where bit 0 represents pin 32.
#define CONF_SLCD_LPENH (\
        (uint32_t)1 << (32 - 32) | \
        (uint32_t)1 << (33 - 32) | \
        (uint32_t)1 << (34 - 32) | \
        (uint32_t)1 << (35 - 32) | \
        (uint32_t)1 << (42 - 32) | \
        (uint32_t)1 << (43 - 32) | \
        (uint32_t)1 << (48 - 32) | \
        (uint32_t)1 << (49 - 32) | \
        (uint32_t)1 << (50 - 32) | \
        (uint32_t)1 << (51 - 32) | 0)


// 9-pin connector
#define A0 GPIO(GPIO_PORTB, 4)
#define WATCH_A0_EIC_CHANNEL 4
#define A1 GPIO(GPIO_PORTB, 1)
#define WATCH_A1_EIC_CHANNEL 1
#define A2 GPIO(GPIO_PORTB, 2)
#define WATCH_A2_EIC_CHANNEL 2
#define A3 GPIO(GPIO_PORTB, 3)
#define WATCH_A3_EIC_CHANNEL 3
#define A4 GPIO(GPIO_PORTB, 0)
#define WATCH_A4_EIC_CHANNEL 0
#define SDA GPIO(GPIO_PORTB, 30)
#define SCL GPIO(GPIO_PORTB, 31)

// aliases for as A3/A4; these were mentioned as D0/D1 in early documentation.
#define D0 GPIO(GPIO_PORTB, 3)
#define D1 GPIO(GPIO_PORTB, 0)

// interrupt mapping
#define EXT_IRQ_AMOUNT 6
#define CONFIG_EIC_EXTINT_MAP {0, PIN_PB00}, {1, PIN_PB01}, {2, PIN_PA02}, {3, PIN_PB03}, {5, PIN_PB05}, {7, PIN_PA07},

#endif // PINS_H_INCLUDED
